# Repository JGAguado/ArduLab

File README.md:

[![GitHub Release][releases-shield]][releases]
[![License][license-shield]](LICENSE)

[![Project Maintenance][maintenance-shield]][maintenance]
[![BuyMeCoffee][buymecoffee-shield]][buymecoffee]

# ArduLab

The ArduLab board is a robotic platform designed for the ICAI Technological Campus. It has been created with educational purposes for developing robotic proyects based on de [Arduino](https://www.arduino.cc) environment.

## Features
* Atmega32U4 microcontroller (same as Arduino Leonardo)
* RGB Led
* LDR
* Buzzer
* Pushbutton
* DC Motor driver (H-Bridge)
* LiPo charging system
* Bluetooth connectivity (HC-05)

It supports the [Itead Nextion Displays](https://www.itead.cc/display/nextion.html) via serial port and also can be plugged directly to the [ElectroLab](https://github.com/SpaceDIY/ElectroLab) board to expand it's functions!

## Project tree

<li><a href="./Hardware/">Hardware</a></li>
<li><a href="./Firmware/">Firmware</a></li>
<li><a href="./Documentation/">Documentation</a></li>

<li><a href="./README.md">README.md</a></li>

[releases-shield]: https://img.shields.io/github/release/JGAguado/ArduLab.svg?style=for-the-badge
[releases]: https://github.com/JGAguado/ArduLab/releases

[license-shield]: https://img.shields.io/badge/License-CC%20BY--NC--SA%204.0-lightgrey.svg?style=for-the-badge

[maintenance-shield]: https://img.shields.io/badge/maintainer-J.%20G.%20Aguado-blue.svg?style=for-the-badge
[maintenance]: https://github.com/JGAguado

[buymecoffee-shield]: https://img.shields.io/badge/buy%20me%20a%20coffee-support-yellow.svg?style=for-the-badge
[buymecoffee]: https://www.buymeacoffee.com/J.G.Aguado

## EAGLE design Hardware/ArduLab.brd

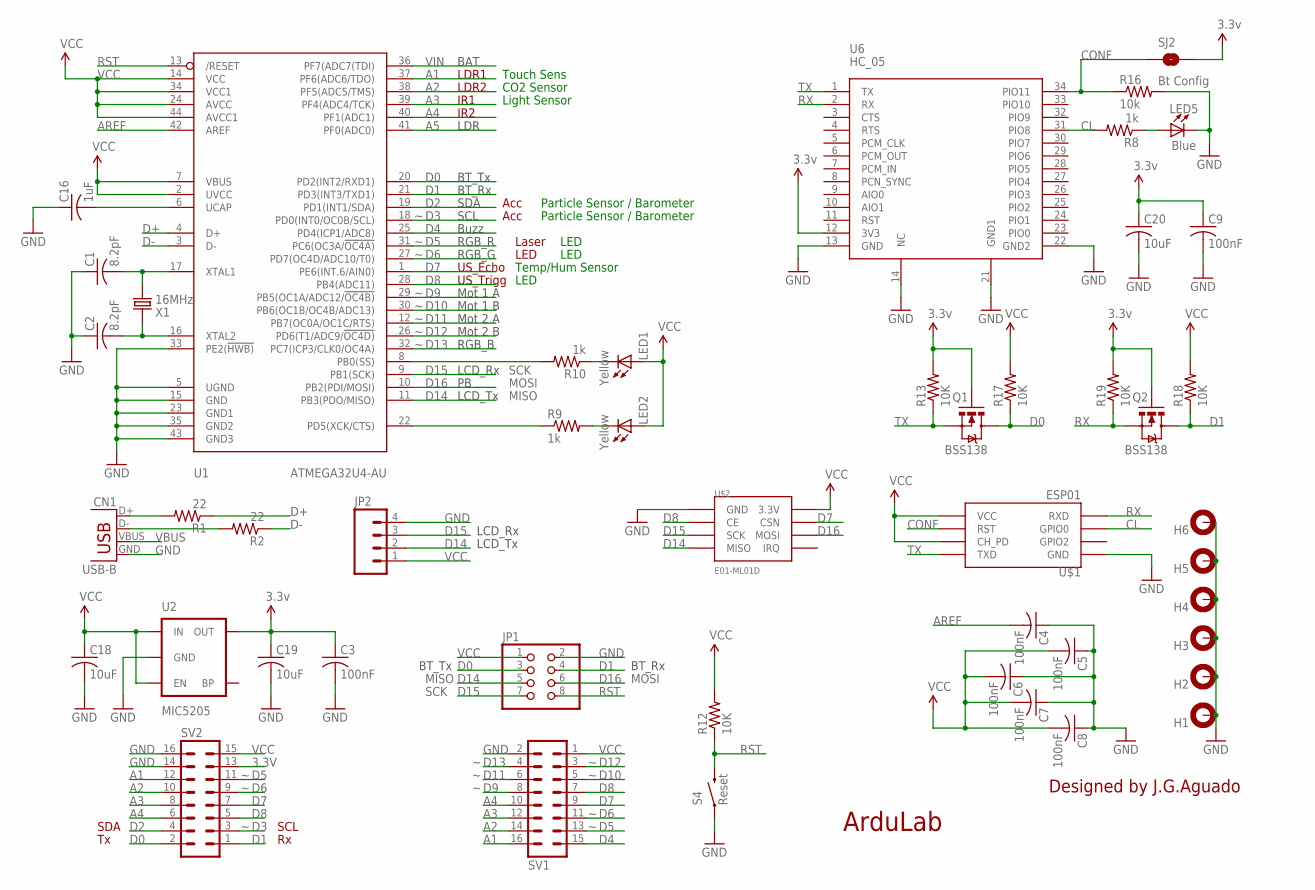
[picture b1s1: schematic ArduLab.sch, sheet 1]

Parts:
C1, C2: 8.2pF; C1206
C3, C4, C5, C6, C7, C8, C9: 100nF; C1206
C16: 1uF; C1206
C18, C19, C20: 10uF; C1206
CN1: USB-B; USB-B-PTH
H1, H2, H3, H4, H5, H6: MOUNT-PAD-ROUND3.2; 3,2-PAD
JP1: PINHD-2X4; 2X04
JP2: M04SMD; 1X04-SMD
LED1, LED2: Yellow; LED1206
LED5: Blue; LED1206
Q1, Q2: BSS138; SOT23-3
R1, R2: 22; R1206
R8, R9, R10: 1k; R1206
R12, R13, R17, R18, R19: 10K; R1206
R16: 10k; R1206
S4: Reset; TACTILE_SWITCH_TALL
SJ2: Bt Config; SJ_ROUND
SV1, SV2: MA08-2
U1: ATMEGA32U4-AU; TQFP44
U2: MIC5205; SOT23-5
U6: HC_05; BLUETOOTH_SMD
U$1: ESP01
U$2: E01-ML01D
X1: 16MHz; 2P-SMD-5X3.2

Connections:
3.3V: C3.1, C9.1, C19.1, C20.1, Q1.1 (G), Q2.1 (G), R13.2, R19.2, SJ2.2, SV2.13, U2.5 (OUT), U6.12 (3V3), U$1.CH_PD, U$1.VCC, U$2.P$2 (3.3V)
A1: SV1.16, SV2.12, U1.37 (PF6(ADC6/TDO))
A2: SV1.14, SV2.10, U1.38 (PF5(ADC5/TMS))
A3: SV1.12, SV2.8, U1.39 (PF4(ADC4/TCK))
A4: SV1.10, SV2.6, U1.40 (PF1(ADC1))
A5: U1.41 (PF0(ADC0)); also elsewhere on the board
AREF: C4.2, U1.42 (AREF)
CL: R8.2, U6.31 (PIO8), U$1.GPIO0
CONF: R16.1, SJ2.1, U6.34 (PIO11), U$1.RST
D0: JP1.3, Q1.3 (D), R17.1, SV2.2, U1.20 (PD2(INT2/RXD1))
D1: JP1.4, Q2.3 (D), R18.1, SV2.1, U1.21 (PD3(INT3/TXD1))
D2: SV2.4, U1.19 (PD1(INT1/SDA))
D3: SV2.3, U1.18 (PD0(INT0/OC0B/SCL))
D4: SV1.15, U1.25 (PD4(ICP1/ADC8)); also elsewhere on the board
D5: SV1.13, SV2.11, U1.31 (PC6(OC3A/!OC4A)); also elsewhere on the board
D6: SV1.11, SV2.9, U1.27 (PD7(OC4D/ADC10/T0)); also elsewhere on the board
D7: SV1.9, SV2.7, U1.1 (PE6(INT.6/AIN0)), U$2.P$4 (CSN)
D8: SV1.7, SV2.5, U1.28 (PB4(ADC11)), U$2.P$3 (CE)
D9: SV1.8, U1.29 (PB5(OC1A/ADC12/!OC4B)); also elsewhere on the board
D10: SV1.5, U1.30 (PB6(OC1B/OC4B/ADC13)); also elsewhere on the board
D11: SV1.6, U1.12 (PB7(OC0A/OC1C/RTS)); also elsewhere on the board
D12: SV1.3, U1.26 (PD6(T1/ADC9/!OC4D)); also elsewhere on the board
D13: SV1.4, U1.32 (PC7(ICP3/CLK0/OC4A)); also elsewhere on the board
D14: JP1.5, JP2.2, U1.11 (PB3(PDO/MISO)), U$2.P$7 (MISO)
D15: JP1.7, JP2.3, U1.9 (PB1(SCK)), U$2.P$5 (SCK)
D16: JP1.6, U1.10 (PB2(PDI/MOSI)), U$2.P$6 (MOSI); also elsewhere on the board
D17/PB0/RXLED: R10.2, U1.8 (PB0(SS))
D+: R1.1, U1.4 (D+)
D-: R2.1, U1.3 (D-)
GND: C1.1, C2.1, C3.2, C4.1, C5.1, C6.1, C7.1, C8.1, C9.2, C16.1, C18.2, C19.2, C20.2, CN1.GND, H1.B3,2, H2.B3,2, H3.B3,2, H4.B3,2, H5.B3,2, H6.B3,2, JP1.2, JP2.4, LED5.C, R16.2, S4.A2 (1), SV1.2, SV2.14, SV2.16, U1.5 (UGND), U1.15 (GND), U1.23 (GND1), U1.33 (PE2(!HWB)), U1.35 (GND2), U1.43 (GND3), U2.2 (GND), U6.13 (GND), U6.14 (NC), U6.21 (GND1), U6.22 (GND2), U$1.GND, U$2.P$1 (GND); also elsewhere on the board
unnamed: C1.2, U1.17 (XTAL1), X1.2
unnamed: C2.2, U1.16 (XTAL2), X1.1
unnamed: LED2.C, R9.2
unnamed: LED1.C, R10.1
unnamed: CN1.D+, R1.2
unnamed: CN1.D-, R2.2
unnamed: LED5.A, R8.1
PD5/TXLED: R9.1, U1.22 (PD5(XCK/CTS))
RST: JP1.8, R12.1, S4.B2 (2), U1.13 (/RESET)
RX: Q2.2 (S), R19.1, U6.2 (RX), U$1.RX (RXD)
TX: Q1.2 (S), R13.1, U6.1 (TX), U$1.TX (TXD)
UCAP: C16.2, U1.6 (UCAP)
VBUS: CN1.VBUS; also elsewhere on the board
VCC: C5.2, C6.2, C7.2, C8.2, C18.1, JP1.1, JP2.1, LED1.A, LED2.A, R12.2, R17.2, R18.2, SV1.1, SV2.15, U1.2 (UVCC), U1.7 (VBUS), U1.14 (VCC), U1.24 (AVCC), U1.34 (VCC1), U1.44 (AVCC1), U2.1 (IN), U2.3 (EN); also elsewhere on the board
VIN: U1.36 (PF7(ADC7(TDI)); also elsewhere on the board

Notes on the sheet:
ArduLab
Designed by J.G.Aguado
SCK
MOSI
MISO
BAT
BT_Tx
BT_Rx
Acc
Buzz
Mot 1 A
Mot 1 B
Mot 2 B
Mot 2 A
RGB_B
LCD_Tx
LCD_Rx
LDR1
LDR2
IR1
IR2
SDA
SCL
Laser
LED
US_Echo
US_Trigg
Touch Sens
CO2 Sensor
Light Sensor
Particle Sensor / Barometer
Temp/Hum Sensor
RGB_R
RGB_G
LDR

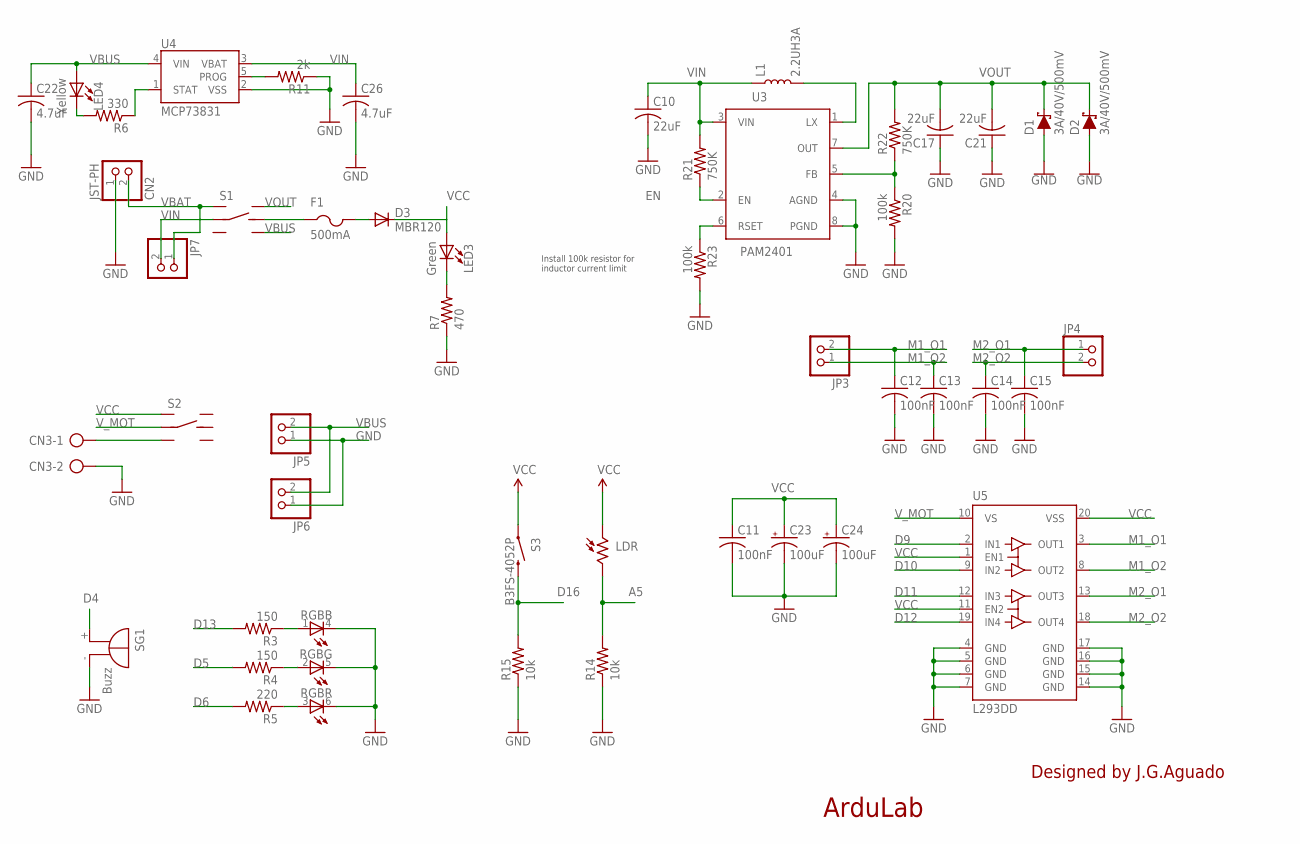
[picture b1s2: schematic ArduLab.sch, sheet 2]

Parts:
C10, C17, C21: 22uF; C1206
C11, C12, C13, C14, C15: 100nF; C1206
C22, C26: 4.7uF; C3216
C23, C24: 100uF; EIA3528-KIT
CN2: JST-PH; JST-PH-2-SMT
CN3: AK500/2
D1, D2: 3A/40V/500mV; SMA-DIODE
D3: MBR120; SOD123
F1: 500mA; R1206
JP3, JP4, JP5, JP6, JP7: PINHD-1X2; 1X02
L1: 2.2UH3A; INDUCTOR_4X4MM
LDR: VT20N1; TO46-VT200
LED3: Green; LED1206
LED4: Yellow; LED1206
R3, R4: 150; R1206
R5: 220; R1206
R6: 330; R1206
R7: 470; R1206
R11: 2k; R1206
R14, R15: 10k; R1206
R20, R23: 100k; R1206
R21, R22: 750K; R1206
RGB: OVSTRGBBCR8_V2
S1, S2: DPDT_JS202011CQN
S3: B3FS-4052P; TACTILE-SMD-12MM
SG1: Buzz; F/HMB
U3: PAM2401; MSOP8
U4: MCP73831; SOT23-5
U5: L293DD; SO20

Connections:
A5: LDR.2, R14.2; also elsewhere on the board
D4: SG1.+; also elsewhere on the board
D5: R4.2; also elsewhere on the board
D6: R5.2; also elsewhere on the board
D9: U5.2 (IN1); also elsewhere on the board
D10: U5.9 (IN2); also elsewhere on the board
D11: U5.12 (IN3); also elsewhere on the board
D12: U5.19 (IN4); also elsewhere on the board
D13: R3.2; also elsewhere on the board
D16: R15.2, S3.3 (2); also elsewhere on the board
EN: R21.1, U3.2 (EN)
GND: C10.2, C11.2, C12.2, C13.2, C14.2, C15.2, C17.1, C21.1, C22.2, C23.C (-), C24.C (-), C26.2, CN2.1 (2), CN3.2, D1.A, D2.A, JP5.1, JP6.1, R7.1, R11.1, R14.1, R15.1, R20.2, R23.2, RGB.4 (C), RGB.5 (C), RGB.6 (C), SG1.-, U3.4 (AGND), U3.8 (PGND), U4.2 (VSS), U5.4 (GND), U5.5 (GND), U5.6 (GND), U5.7 (GND), U5.14 (GND), U5.15 (GND), U5.16 (GND), U5.17 (GND); also elsewhere on the board
M1_O1: C12.1, JP3.2, U5.3 (OUT1)
M1_O2: C13.1, JP3.1, U5.8 (OUT2)
M2_O1: C15.1, JP4.1, U5.13 (OUT3)
M2_O2: C14.1, JP4.2, U5.18 (OUT4)
unnamed: R20.1, R22.1, U3.5 (FB)
unnamed: F1.1, S1.5 (RC)
unnamed: L1.P$2 (2), U3.1 (LX)
unnamed: R23.1, U3.6 (RSET)
unnamed: LED4.C, R6.2
unnamed: R11.2, U4.5 (PROG)
unnamed: R6.1, U4.1 (STAT)
unnamed: LED3.C, R7.2
unnamed: D3.A, F1.2
unnamed: R3.1, RGB.1 (A)
unnamed: R4.1, RGB.2 (A)
unnamed: R5.1, RGB.3 (A)
VBAT: CN2.2 (1), JP7.1, S1.1 (L1)
VBUS: C22.1, JP5.2, JP6.2, LED4.A, S1.6 (R2), U4.4 (VIN); also elsewhere on the board
VCC: C11.1, C23.A (+), C24.A (+), D3.C, LDR.1, LED3.A, S2.1 (L1), S3.1, U5.1 (EN1), U5.11 (EN2), U5.20 (VSS); also elsewhere on the board
VIN: C10.1, C26.1, JP7.2, L1.P$1 (1), R21.2, S1.2 (LC), U3.3 (VIN), U4.3 (VBAT); also elsewhere on the board
VOUT: C17.2, C21.2, D1.C, D2.C, R22.2, S1.4 (R1), U3.7 (OUT)
V_AUX: CN3.1, S2.3 (L2)
V_MOT: S2.2 (LC), U5.10 (VS)

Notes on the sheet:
ArduLab
Designed by J.G.Aguado
Install 100k resistor for inductor current limit

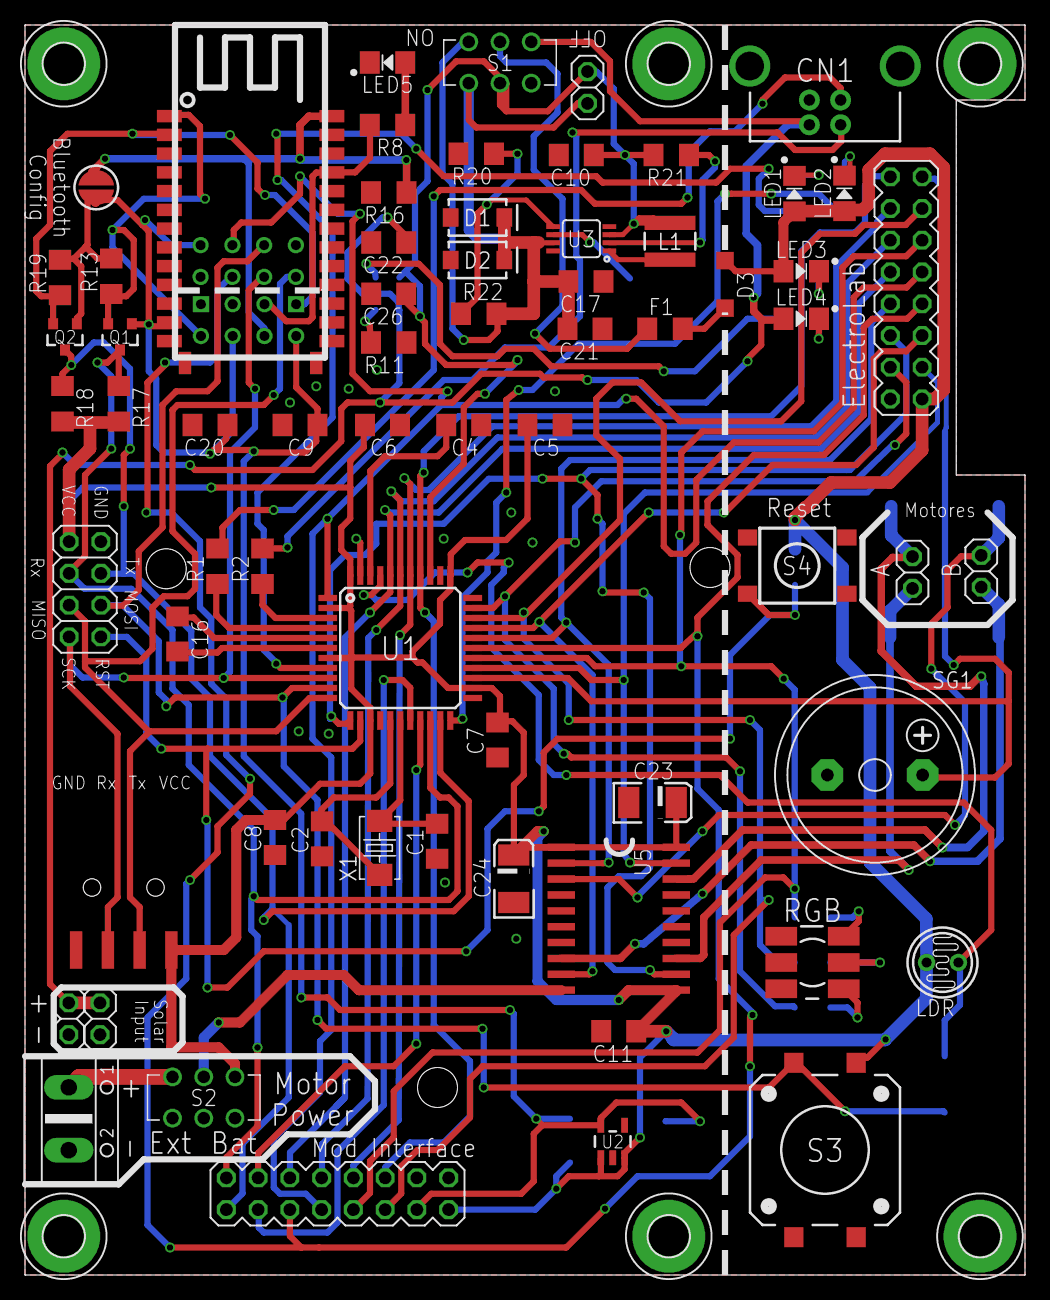
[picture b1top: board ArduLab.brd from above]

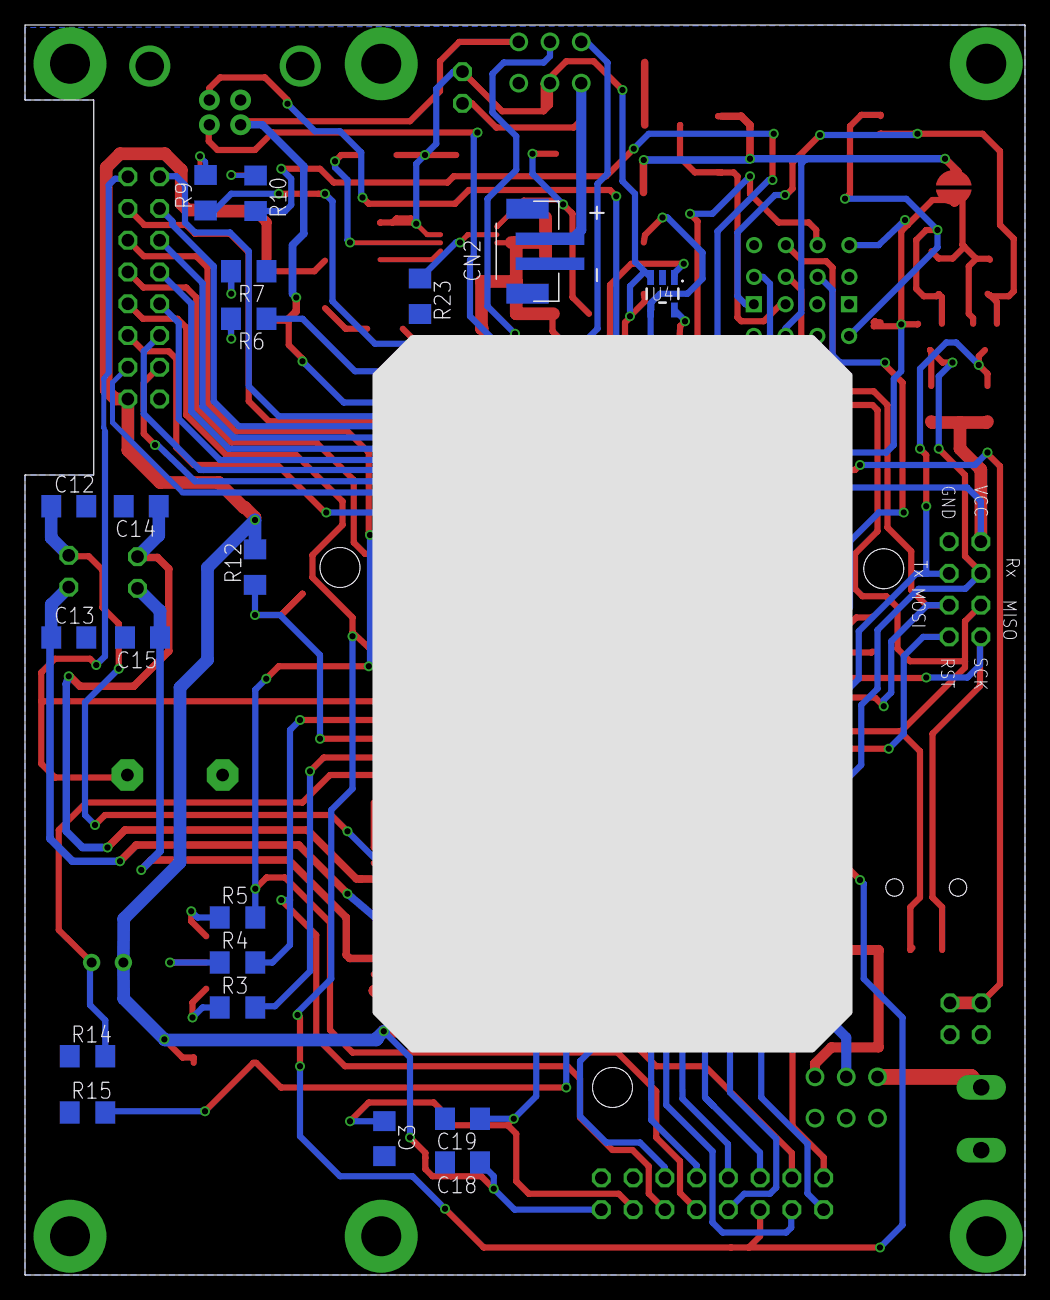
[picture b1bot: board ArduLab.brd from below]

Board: 2 copper layers, 80.0 x 100.0 mm, 95 parts (20 on the bottom side), 66 nets.

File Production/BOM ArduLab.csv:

No.;Design Ref;Description;Value;Package;Qty;Notes;
1;C1; C2;Capacitor;8.2pF;C1206;2;
2;C3 - C15;Capacitor;100nF (6;3V);C1206;13;
3;C16;Capacitor;1uF (6;3V);C1206;1;
4;C17; C21;Capacitor;22uF (6;3V);C1206;2
5;C18 - C20;Capacitor;10uF (6;3V);C1206;3;
6;C22; C26;Polarized Capacitor;4.7uF  (6;3V);C1206;2
7;C23; C24;Polarized Capacitor;100uF  (6;3V);3528;2
8;CN1;USB Type B Female;USB-B;USB-B-PTH;1;;
9;CN2;LiPo Battery JST Connector;JST-PH;JST-PH-2-SMT;1;;
10;D1; D2;Diode Schottky;B340A;SMA;2;3A/40V/500mV
11;D3;Diode;MBR120;SOD-123;1;;
12;JP1;Pin header 2;54 - Straight;2x04 Male;Through Hole;1;
13;JP2;Pin header 2;54 - Right Angle;1x04 Male;SMD;1;4Ucon Item No: 11029 
14;JP3; JP4;Pin header 2;54 - Straight;1x02;Through Hole;2
15;L1;Inductor 4x4mm;2;2uH;Inductor 4x4mm;1;IFSC1515AHER2R2M01
16;LDR;Photocell;;GL5528;1;;
17;LED1; LED2; LED4;Led;Yellow;1206;3
18;LED3;Led;Green;1206;1;;
19;LED5;Led;Blue;1206;1;;
20;Q1; Q2;Mosfet N-Channel;BSS138;SOT23-3;2;
21;R1; R2;Resistor;22;R1206;2;
22;R3; R4;Resistor;150;R1206;2;
23;R5;Resistor;220;R1206;1;;
24;R6;Resistor;330;R1206;1;;
25;R7;Resistor;470;R1207;1;;
26;R8 - R10;Resistor;1k;R1206;3;;
27;R11;Resistor;2k;R1206;1;;
28;R12 - R19;Resistor;10k;R1206;8;;
29;R20;Resistor;100k;R1206;1;;
30;R21; R22;Resistor;750k;R1206;2;
31;RGB;RGB LED ;PLCC-6;SLV6A-FKB-CK1P1G1BB7R3R3;1;;
32;S1;Switch 2 pos - Right Angle;JS202011AQN;Through Hole;2;Mouser Part No: 611-JS202011AQN;
33;S2;Switch 2 pos;JS202011AQN;Through Hole;2;Mouser Part No: 611-JS202011AQN;
34;S3;Pushbutton ;B3FS-4052P;SMD 12x12mm;1;Mouser Part No: 653-B3FS-4052P;
35;S4;Pushbutton ;2-1437565-8;SMD 6x6mm;;Mouser Part No: 506-2-1437565-8;
36;SG1;Buzzer;5VDC ;Diam 12mm;1;Mouser Part No: 490-CMI-1275C-050;
37;SV1;Pin header 2;54 - Right Angle;SFH11-PBPC-D08-RA-BK;;1;Sullins Part No: SFH11-PBPC-D08-RA-BK
38;SV2;Pin header 2;54 - Right Angle;SBH11-PBPC-D08-RA-BK;;1;Sullins Part No: SBH11-PBPC-D08-RA-BK
39;T1;Bipolar Transistor;MMUN2133LT1G;SOT23;1;;
40;U1;Microcontroller;ATMEGA32U4-AU;TQFP44;1;Is it possible for you to bootload it? ;
41;U2;Voltage regulator;MIC5205;SOT23-5;1;;
42;U3;Voltage booster;PAM2401;MSOP8;1;;
43;U4;Battery Management Charge IC;MCP73831;SOT23-5;1;;
44;U5;Motor Driver;L293DD;SO20;1;;
45;X1;Crystal;16MHz;2P-SMD-5X3.2;1;Mouser Part No: 815-ABM3-16-D2Y-T;
46;;Screwed spacer sleeve;M2x10;;4;http://www.tme.eu/gb/details/tfm-m2x10_dr221/metal-spacers/d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;

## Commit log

2017-12-26 Initial commit V1
    First prototype board
2017-12-26 Fixed bug: Battery connector polarity
2017-12-26 Modified: Center pad of U3 (TPS61030) wired to ground
2017-12-27 Bluetooth-microcontroller communication improved with shift level conversor.
2017-12-27 Added support for ESP8266-01
2017-12-28 LiPo power boosting circuit based in PAM2401 IC
2017-12-29 Added support for Serial interface in Mod connector
2017-12-29 Updated Mod Interface for RadioLab compatibility
2017-12-29 New Mod Interface position layout (25x6.5mm)
2018-01-14 SCH and BRD updated. Added Production files (GERBER, BOM and CENTROID)
2018-01-17 Update gerber for production
2018-02-01 Added drill hole for battery holding.
2018-02-03 Minor SCH Updates: V1.0 label removed
2018-02-03 Minor BRD updates and Production files regenerated: -Layout correction.
2018-02-03 Schematics PDF uploaded
2018-02-03 Centroid update
2018-02-09 Added R23 (100k) as optional resistor for inductor current limit
2018-02-22 Updated Production files
2018-04-28 Added PTC reset fuse 6V 500mA. Package 1206. Part number: 1206L050YR
2018-04-28 Connection between pin A0 and battery voltage pin for monitoring the battery status.
2018-04-28 2.4GHz RF ML01D Module Integration
2018-05-02 Updated components silkscreen layout
2018-05-19 Added Schematics.pdf
2018-05-19 Added first version of ArduLab library with basics example
2018-05-19 Updated Basics example
2019-05-06 Added Documentation and Illustrations
2022-04-15 Updated structure

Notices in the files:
parts and their libraries:
SparkFun-PowerIC: Licensing: Creative Commons ShareAlike 4.0 International - https://creativecommons.org/licenses/by-sa/4.0
